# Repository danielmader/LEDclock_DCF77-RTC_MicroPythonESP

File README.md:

# LEDclock_DCF77-RTC_MicroPythonESP

MicroPython-LED-Uhr auf MAX7219-Punktmatrix-Modulen mit DCF77-Zeitzeichenempfänger,
batteriegepufferter externer RTC (RV-8263), Temperatur-/Luftfeuchtesensor (SHT31)
und Helligkeitssensor (TEMT6000) zur automatischen Display-Dimmung.

Es gibt zwei Hardware-Varianten mit identischer Software:

* **Board 1: ESP-WROOM-32** (NodeMCU)
* **Board 2: ESP32-S3-WROOM-1** (N16R8)

Boardvarianten & Pinbelegung
----------------------------

Die Pinbelegung liegt nicht mehr im Code, sondern in JSON-Dateien in `src/`:

* `board_esp-wroom-32.json` — Board 1
* `board_esp32-s3-wroom-1.json` — Board 2

Das Modul `src/boardconfig.py` erkennt das Board zur Laufzeit automatisch
(über `os.uname().machine`) und lädt die passende Datei. Es genügt also, beide
JSON-Dateien mit auf das Gerät zu kopieren. Für Sonderaufbauten kann eine Datei
`board.json` auf dem Gerät abgelegt werden, die dann Vorrang hat.

| Funktion / Peripherie | Signal      | ESP-WROOM-32 | ESP32-S3-WROOM-1 | Anmerkung |
| :-------------------- | :---------- | :----------- | :--------------- | :-------- |
| I2C (RV-8263, SHT31)  | SDA         | GPIO23       | GPIO8            | 50 kHz, interne Pull-ups |
|                       | SCL         | GPIO22       | GPIO9            | |
| TEMT6000              | ADC         | GPIO36 (ADC1_CH0) | GPIO4 (ADC1_CH3) | zwingend ADC1 (ADC2 kollidiert mit Wi-Fi) |
| DCF77                 | DATA        | GPIO13       | GPIO14           | Eingang mit Pull-up |
| MAX7219               | DIN (MOSI)  | GPIO19       | GPIO42           | S3: GPIO19/20 sind USB! |
|                       | SCLK        | GPIO5        | GPIO1            | |
|                       | CS          | GPIO18       | GPIO2            | |
| MAX7219 Power ON/OFF  | GPIO out    | –            | GPIO21           | optional (`null` in JSON = nicht beschaltet) |
| Status-LED            | GPIO out    | GPIO2        | –                | S3-DevKit hat nur RGB-LED (GPIO48) |

Wichtige Hinweise zum ESP32-S3 (Details in `hardware/Pinout Proposal.md`):

* **GPIO19/20** sind das native USB-Interface — nicht extern beschalten.
* **GPIO0** ist Strapping-Pin (Bootloader) — nicht als Power-Control verwenden.
* **N16R8 (8 MB Octal-PSRAM):** GPIO33–37 sind intern belegt; die herausgeführten
  GPIO35–37 dürfen **nicht** beschaltet werden.

Batterie-Backup für RV-8263 RTC
-------------------------------

Anschlüsse am Beispiel ESP-WROOM-32 (beim ESP32-S3: SDA = GPIO8, SCL = GPIO9):

    ESP-WROOM-32 NodeMCU

    VCC (3.3V ESP) -----------------+-------+-------+
                                    |       |       |
                                    [R1]    [R2]    [D1] (Schottky)
                                    10k     10k     |
                                    |       |       |
    SDA (GPIO 23) ------------------+----------------------- SDA (RV-8263)
                                            |       |
    SCL (GPIO 22) --------------------------+--------------- SCL (RV-8263)
                                                    |
                                                    +------- VCC (RV-8263)
                                                    |
    Batterie (+) ----------[D2] (Schottky) ---------+
    (Knopfzelle)

    GND (ESP) --------------------------------------+------- VSS (RV-8263)
                                                    |
    Batterie (-) -----------------------------------+

* R1 = R2: 10 kOhm
* D1 = D2: Schottky-Diode BAT 42/43 oder BAT 86

Schaltbild Peripherie (ohne Backup-Batterie)
--------------------------------------------

Verdrahtungspläne für beide Boards liegen in `hardware/`:

* [Wiring Diagram ESP-WROOM-32](./hardware/Wiring%20Diagram_ESP-WROOM-32.png) ([PDF](./hardware/Wiring%20Diagram_ESP-WROOM-32.pdf))
* [Wiring Diagram ESP32-S3-WROOM-1](./hardware/Wiring%20Diagram_ESP32-S3-WROOM-1.png) ([PDF](./hardware/Wiring%20Diagram_ESP32-S3-WROOM-1.pdf))

ASCII-Übersicht am Beispiel ESP-WROOM-32:

    ESP-WROOM-32 NodeMCU

    3V3  -----------------------------------+------------------+------------------+
                                            |                  |                  |
                                            |                  |                  +---- VCC (MAX7219)
                                            |                  +----------------------- VCC (TEMT6000)
                                            +------------------------------------------ VCC (I2C: RV-8263, SHT31)

    5V (VIN) --------------------------------------------------- VCC (DCF77)

    GND  -----------------------------------+------------------+------------------+------------------+
                                            |                  |                  |                  |
                                            |                  |                  |                  +---- GND (MAX7219)
                                            |                  |                  +---- GND (DCF77)
                                            |                  +----------------------- GND (TEMT6000)
                                            +------------------------------------------ VSS (I2C: RV-8263, SHT31)

    GPIO23 (SDA) ---------------------------+------------------ SDA (RV-8263)
                                            |
                                            +------------------ SDA (SHT31)

    GPIO22 (SCL) ---------------------------+------------------ SCL (RV-8263)
                                            |
                                            +------------------ SCL (SHT31)

    GPIO36 (ADC) ------------------------------------------------ AO/OUT (TEMT6000)

    GPIO13 -------------------------------------------------------- DATA/OUT (DCF77)

    GPIO19 (SPI MOSI) ------------------------------------------------ DIN (MAX7219)

    GPIO18 (SPI CS) -------------------------------------------------- CS (MAX7219)

    GPIO5  (SPI SCLK) ------------------------------------------------ SCLK (MAX7219)

Hinweis DCF77 Versorgung
------------------------

- Der DCF77-Empfänger kann mit 5V versorgt werden; das ist für die Signalqualität
  oft etwas robuster.
- Wichtig: Das DCF77-Datensignal muss dann auf 3.3V-Pegel zum ESP32 angepasst
  werden (Spannungsteiler, Pegelwandler oder Open-Collector mit 3.3V Pull-up).
- Läuft das Modul sauber mit 3.3V, ist das meist die einfachste und sicherste
  Lösung, weil kein Pegelwandler nötig ist.
- DCF77-Empfänger reagieren empfindlich auf Wi-Fi-Störungen und sollten räumlich
  getrennt vom ESP32 platziert werden.

Software
--------

Die Skripte liegen in `src/`:

* `main.py` — Hauptprogramm (asyncio-Tasks: DCF77-Empfang, Zeit-Sync, Sensorik, Anzeige)
* `boardconfig.py` — lädt die Pinbelegung aus `board_*.json` (Auto-Erkennung)
* `dcf77.py` — DCF77-Dekoder
* `rv8263.py` — Treiber externe RTC RV-8263
* `sht31.py` — Treiber Temperatur-/Feuchtesensor SHT31
* `temt6000.py` — Treiber Helligkeitssensor TEMT6000
* `max7219wrapper.py`, `characters.py` — Display-Ansteuerung und Fonts
* `lib/max7219.py` — MAX7219-Basistreiber (mcauser), auf dem Gerät nach `/lib`
* `playground/` — Diagnose-Skripte (DCF77-Analyzer, I2C-Diagnose)

Deployment z.B. mit `mpremote`: alle `.py` aus `src/` sowie **beide**
`board_*.json` ins Wurzelverzeichnis des Geräts kopieren, `src/lib/max7219.py`
nach `/lib/max7219.py`.

Entwicklung: Linting & Typechecking
-----------------------------------

### Einrichtung der venv

Die Konfigurationen (`pyrightconfig.json`, `scripts/update-typeshed.sh`) erwarten
die venv unter `.venv` mit **Python 3.11**. Einrichtung wahlweise mit pip oder uv:

    ## Variante A: pip/venv
    python3.11 -m venv .venv
    .venv/bin/pip install -r requirements.txt

    ## Variante B: uv
    uv venv --python 3.11 .venv
    uv pip install -r requirements.txt

    ## Danach in beiden Fällen: kombiniertes Typeshed für ty erzeugen
    ./scripts/update-typeshed.sh

`requirements.txt` enthält alles Nötige:

* `micropython-esp32-stubs` — Typ-Stubs für `machine`, `network`, `time.ticks_ms()`
  usw. (zieht `micropython-stdlib-stubs` automatisch mit)
* `basedpyright` — Typechecker, gleiche Engine wie Pylance
* `ty` — Typechecker von Astral (Hersteller von ruff/uv)
* `ruff` — Linter (Import-Sortierung, Code-Stil, Komplexität)

*(Hinweis: Das npm-Paket `pyright` selbst braucht eine Node-Runtime mit
`libatomic.so.1` — `basedpyright` bringt dagegen alles als Python-Wheel mit
und liest dieselbe `pyrightconfig.json`.)*

### Checker ausführen

    .venv/bin/basedpyright src    ## Konfiguration: pyrightconfig.json
    .venv/bin/ty check            ## Konfiguration: pyproject.toml [tool.ty]
    .venv/bin/ruff check src      ## Linter, Konfiguration: pyproject.toml [tool.ruff]

Alle drei müssen fehlerfrei durchlaufen (Stand der letzten Bereinigung:
0 Fehler / "All checks passed").

### Wie die Stub-Auflösung funktioniert (wichtig bei Problemen)

Die MicroPython-Stubs liegen nach der Installation **flach** in den
site-packages (`time.pyi`, `machine.pyi`, ...), zusätzlich liefert
`micropython-stdlib-stubs` ein partielles `stdlib/`-Verzeichnis (u.a. `asyncio`
mit `sleep_ms`). Die beiden Checker finden sie unterschiedlich:

* **basedpyright/Pylance:** über `stubPath` **und** `typeshedPath` in
  `pyrightconfig.json` — beide zeigen auf
  `.venv/lib/python3.11/site-packages`. Bei einem Wechsel der Python-Version
  müssen diese Pfade angepasst werden!
* **ty:** kennt keinen `stubPath`, sondern nur ein komplettes Ersatz-Typeshed
  (`[tool.ty.environment].typeshed = ".typeshed"` in `pyproject.toml`).
  `scripts/update-typeshed.sh` baut dieses Verzeichnis aus den installierten
  Stubs zusammen (stdlib-Stubs + das dort fehlende `time.pyi`).
  **Nach jedem Update der Stubs erneut ausführen:**

      .venv/bin/pip install -U micropython-esp32-stubs   ## bzw. uv pip install -U ...
      ./scripts/update-typeshed.sh

### Bekannte Stolperfallen (ty 0.0.65)

* Das generierte Typeshed darf **nicht** `typings/` heißen (implizites
  Stub-Verzeichnis von ty → Absturz "dependency graph cycle"). Deshalb `.typeshed/`.
* `src` nicht zusätzlich in `[tool.ty.environment].extra-paths` eintragen —
  es ist bereits First-Party-Root, die Doppelung führt ebenfalls zum Absturz.
* ty versteht mypy-Fehlercodes nicht: `# type: ignore[operator]` unterdrückt
  nur Pylance/basedpyright. Für ty muss zusätzlich `# ty: ignore[<regel>]` an
  die Zeile (Beispiele in `main.py` bei der Driftkompensation).
* Ticks sind in den Stubs bewusst opak typisiert (`_TicksMs`): direkte
  Arithmetik wie `ticks_ms() % 1000` wird angemeckert — gewollt ist
  `time.ticks_diff()` / `time.ticks_add()`.

### VSCode

Empfohlene Extensions: **Pylance** (oder basedpyright) und **ty**. Damit die
Extensions die Checker aus der venv verwenden, stehen in der Workspace-Datei
(`*.code-workspace` ist gitignored, ggf. neu anlegen):

    "settings": {
        "python.defaultInterpreterPath": "${workspaceFolder}/.venv/bin/python",
        "ty.importStrategy": "fromEnvironment",
        "basedpyright.importStrategy": "fromEnvironment"
    }

ASCII-Boardplan DIN-Lochraster 32x54 (einseitig, ESP-WROOM-32)
--------------------------------------------------------------

Schienen horizontal, Signale vertikal mit Drahtbruecken.

        +----------------------------------------------------+
    01  |5V==================================================|
        |....................................................|
        |3V3=================================================|
        |....................................................|
    05  |GND=================================================|
        |....................................................|
        |SDA=================================================|
        |SCL=================================================|
        |....................................................|
    10  |...................ESP32 NodeMCU....................|
        |   L01 3V3    o......................o GND    R01   |
        |   L02 RESET  o......................o GPIO23 R02   |
        |   L03 GPIO36 o......................o GPIO22 R03   |
        |   L04 GPIO39 o......................o INT    R04   |
    15  |   L05 GPIO34 o......................o INT    R05   |
        |   L06 GPIO35 o......................o GPIO21 R06   |
        |   L07 GPIO32 o......................o GND    R07   |
        |   L08 GPIO33 o......................o GPIO19 R08   |
        |   L09 GPIO25 o......................o GPIO18 R09   |
    20  |   L10 GPIO26 o......................o GPIO5  R10   |
        |   L11 GPIO27 o......................o GPIO17 R11   |
        |   L12 GPIO14 o......................o GPIO16 R12   |
        |   L13 GPIO12 o......................o GPIO4  R13   |
        |   L14 GND    o......................o GPIO0  R14   |
    25  |   L15 GPIO13 o......................o GPIO2  R15   |
        |   L16 INT    o......................o GPIO15 R16   |
        |   L17 INT    o......................o INT    R17   |
        |   L18 INT    o......................o INT    R18   |
        |   L19 5V     o......................o INT    R19   |
    30  |....................................................|
        |....................................................|
        |....................................................|
        +----------------------------------------------------+

Pinouts
-------

### RV-8263
* NC
* Vss
* NC (CLKOE)
* NC (INT)
* VDD
* NC (CLKOUT)
* SCL
* SDA

### SHT31
* VING
* GND
* SCL
* SDA

### TEMT6000
* OUT
* GND
* VCC

### DCF77
* VIN
* SIG
* GND

### MAX7219
* VCC
* GND
* DIN
* CS
* CLK

Lochrasterplatinenlayout
------------------------

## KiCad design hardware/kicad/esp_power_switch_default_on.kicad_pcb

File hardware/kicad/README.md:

# KiCad files (Lochraster-Variante)

Dieses Verzeichnis enthaelt ein minimales KiCad-Projekt fuer die Schaltung
"5V High-Side mit sicherer 3.3V GPIO-Ansteuerung, Default EIN".

Dateien:
- esp_power_switch_default_on.kicad_pro
- esp_power_switch_default_on.kicad_sch
- esp_power_switch_default_on.kicad_pcb

Hinweise fuer Lochraster:
- Alle Widerstaende sind auf axiale THT-Footprints gesetzt.
- Q2/Q3 sind auf TO-92 gesetzt, Pinout im Datenblatt pruefen.
- Q1 ist auf TO-220 gesetzt. Bei anderem Pinout Source/Drain entsprechend verdrahten.
- Das PCB ist als Placement-Template gedacht (2.54 mm Raster), nicht als Fertigungs-PCB.

Konkrete Bestueckung auf der Template-Platine:
- J1 links oben: Eingang +5V/GND
- J2 rechts oben: Ausgang +V_BAUTEIL/GND
- J3 links mittig: ESP_GPIO, +5V, GND
- Q1 (TO-220) rechts oben
- Q3 (TO-92, PNP) mittig oben
- Q2 (TO-92, NPN) links mittig
- R5 zwischen Q3-Kollektor und Q1-Gate (Gate-Serie)
- R1 von Q1-Gate nach GND (Default EIN)
- R2 von +5V nach Q3-Basis
- R3 vom ESP_GPIO zu Q2-Basis
- R4 von Q2-Basis nach GND

Drahtbruecken (Lochraster, Unterseite):
- +5V: J1.1 -> J3.2 -> Q1.S -> R2.1 -> Q3.E
- GND: J1.2 -> J2.2 -> J3.3 -> Q2.E -> R1.2 -> R4.2
- GPIO: J3.1 -> R3.1
- Q2-Basis-Knoten: R3.2 -> Q2.B -> R4.1
- Q3-Basis-Knoten: R2.2 -> Q3.B -> Q2.C
- Q3-Kollektor-Knoten: Q3.C -> R5.1
- Q1-Gate-Knoten: Q1.G -> R5.2 -> R1.1
- Ausgang: Q1.D -> J2.1

Inbetriebnahme-Test:
- GPIO als Input (Hi-Z): Ausgang EIN
- GPIO auf LOW: Ausgang EIN
- GPIO auf HIGH: Ausgang AUS

Empfohlene Praxis fuer den Aufbau:
- 2-polige Klemmenleisten fuer IN (+5V/GND) und OUT (+V_BAUTEIL/GND).
- Sternfoermige Massefuehrung zwischen ESP-GND, Last-GND und Schaltstufe.
- Kurze Verbindung Gate-Netz (Q1_GATE) und 100 nF nah an der Last.

Schaltlogik:
- GPIO HIGH => AUS
- GPIO LOW oder Hi-Z => EIN (Default)

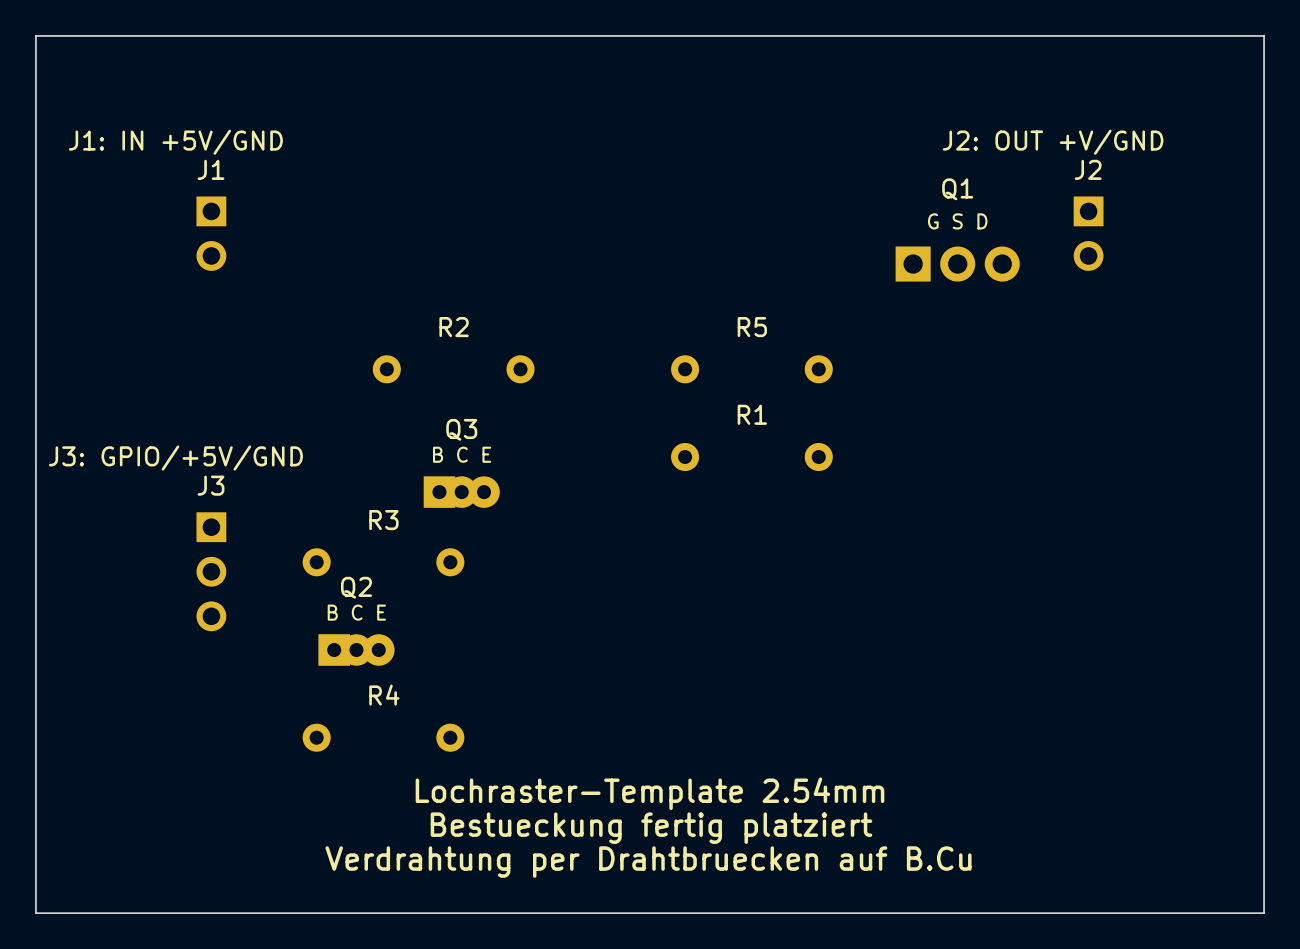
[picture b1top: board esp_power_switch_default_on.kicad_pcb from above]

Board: 2 copper layers, 70.0 x 50.0 mm, 11 parts (0 on the bottom side), 8 nets, no tracks yet.

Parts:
J1: IN_5V_GND; PinHeader_1x02_P2.54mm_Vertical
J2: OUT_V_GND; PinHeader_1x02_P2.54mm_Vertical
J3: ESP_GPIO_HDR; PinHeader_1x03_P2.54mm_Vertical
Q1: FQP27P06; TO-220-3_Vertical
Q2: BC337; TO-92_Inline
Q3: BC327; TO-92_Inline
R1, R4: 100k; R_Axial_DIN0207_L6.3mm_D2.5mm_P7.62mm_Horizontal
R2: 47k; R_Axial_DIN0207_L6.3mm_D2.5mm_P7.62mm_Horizontal
R3: 10k; R_Axial_DIN0207_L6.3mm_D2.5mm_P7.62mm_Horizontal
R5: 220; R_Axial_DIN0207_L6.3mm_D2.5mm_P7.62mm_Horizontal

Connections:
+5V: J1.1, J3.2, Q1.2, Q3.3, R2.1
+V_BAUTEIL: J2.1, Q1.3
ESP_GPIO: J3.1, R3.1
GND: J1.2, J2.2, J3.3, Q2.3, R1.2, R4.2
Q1_GATE: Q1.1, R1.1, R5.2
Q2_BASE: Q2.1, R3.2, R4.1
Q2_COL: Q3.2, R5.1
Q3_BASE: Q2.2, Q3.1, R2.2

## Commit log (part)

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2026-02-22 Initial push, WIP
2026-03-24 Update README.md
    Renamed repo
2026-03-24 More mains, 2x DCF77 libs
2026-03-24 Added links to other projects
2026-03-26 More examples
2026-04-16 Mains cleaned up; custom DCF77 now working
2026-04-16 Consolidated main_asyncio
2026-04-17 Docs, datasheets, wiring (wip)
2026-04-17 Rename main_max7219_bytearray.py to main_MAX7219_bytearray.py
2026-04-17 Rename main_max7219_framebuffer.py to main_MAX7219_framebuffer.py
2026-04-17 Rename main_RV-8263-C7.py to main_RV-8263.py
2026-04-17 Pinout for all accessories
2026-04-19 All peripherals consolidated
2026-04-19 Added link to SHT3x - Sensirion
2026-04-19 WIP: merging DCF77 classes
2026-04-20 Ruffed imports
2026-04-20 Reorganized src
2026-04-20 Renamed modules (lower case); improved dcf77
2026-04-21 v0.1 - Basic Clock Logic
2026-04-22 ESP-Pinout & Boardplan
2026-04-23 Added board layout
2026-04-27 Pinout adjusted for EasyEDA schematics
2026-05-03 Schematics & board layout draft
2026-05-05 Actual board devel
2026-05-07 Perfboard layout v1.0
2026-05-07 Perfboard layout v1.1
2026-05-07 Wiring updated to perfboard layout
2026-05-07 Improvements to RTC register handling
2026-05-08 Consistent wiring diagrams, schematics and perfboard layout v1.0
2026-05-08 Added DCF77 plausibility checks
2026-05-08 Fixed DCF77 plausibilty check
2026-05-10 Character display
2026-05-10 Clock v1.0 RC
2026-05-10 Added photo doc
2026-05-13 Added docstrings and 2nd row (WIP)
2026-05-13 Added 2nd row (sensor values)
2026-05-14 Use only 5x7 font; higher SPI baudrate
2026-05-14 Adjust display brightness
2026-05-17 Added version vor ESP32-S3-WROOM-1
